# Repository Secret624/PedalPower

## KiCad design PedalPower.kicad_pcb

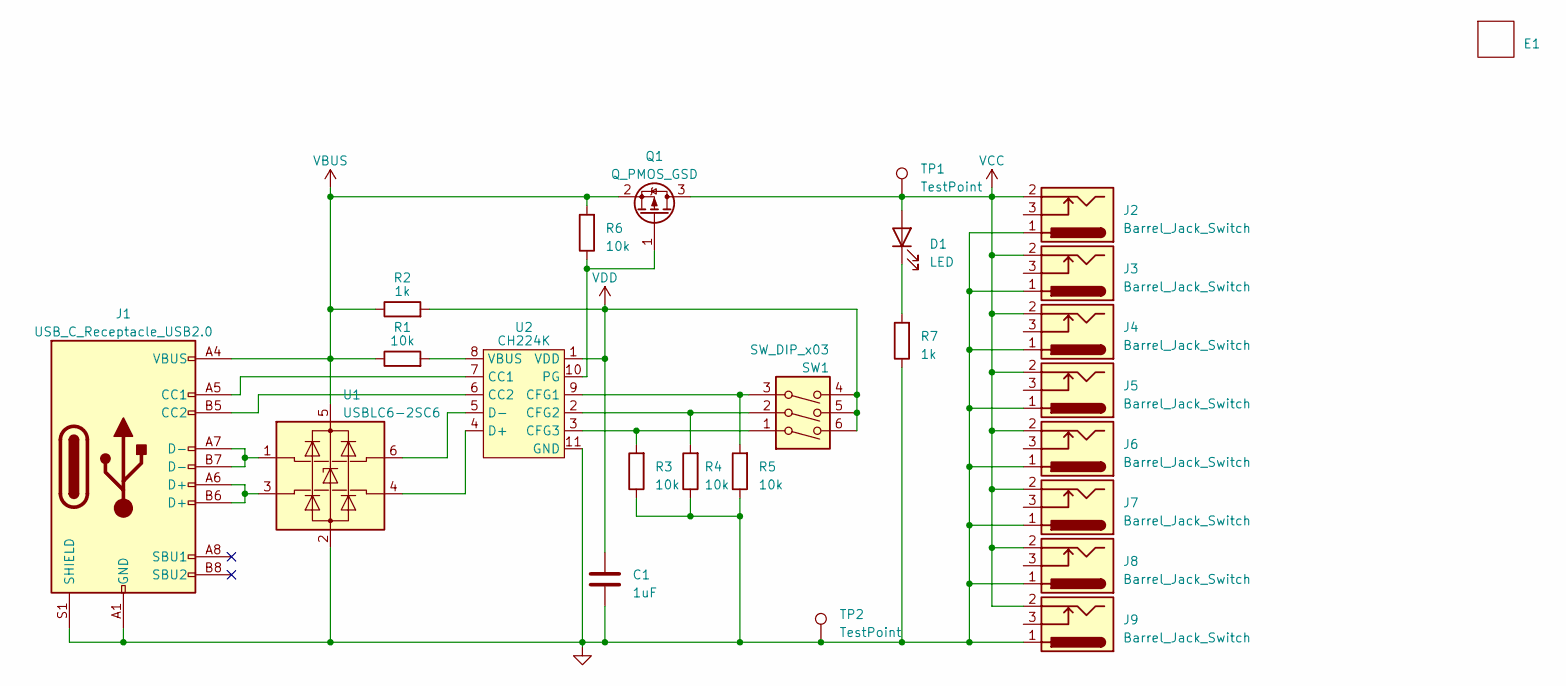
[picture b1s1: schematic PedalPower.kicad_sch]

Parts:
C1: 1uF; C_0805_2012Metric_Pad1.18x1.45mm_HandSolder
D1: LED; LED_0603_1608Metric_Pad1.05x0.95mm_HandSolder
E1: 1591XXMBK
J1: USB_C_Receptacle_USB2.0; USB_C_Receptacle_HRO_TYPE-C-31-M-12; LCSC# C165948
J2, J3, J4, J5, J6, J7, J8, J9: Barrel_Jack_Switch; BarrelJack_Wuerth_6941xx301002
Q1: Q_PMOS_GSD; SOT-23; LCSC# C840062
R1, R3, R4, R5, R6: 10k; R_0805_2012Metric_Pad1.20x1.40mm_HandSolder
R2: 1k; R_0805_2012Metric_Pad1.20x1.40mm_HandSolder
R7: 1k; R_1206_3216Metric_Pad1.30x1.75mm_HandSolder
SW1: SW_DIP_x03; SW_DIP_SPSTx03_Slide_6.7x9.18mm_W7.62mm_P2.54mm_LowProfile; LCSC# C3024969
TP1, TP2: TestPoint; TestPoint_THTPad_4.0x4.0mm_Drill2.0mm
U1: USBLC6-2SC6; SOT-23-6; LCSC# C2687116
U2: CH224K; SSOP-10_3.9x4.9mm_P1.00mm_EP_2.1x3.3; LCSC# C970725

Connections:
GND: C1.2, J1.A1 (GND), J1.A12 (GND), J1.B1 (GND), J1.B12 (GND), J1.S1 (SHIELD), J2.1, J3.1, J4.1, J5.1, J6.1, J7.1, J8.1, J9.1, R3.1, R4.1, R5.1, R7.1, TP2.1, U1.2 (GND), U2.11 (GND)
unnamed: D1.1 (K), R7.2
unnamed: J1.A5 (CC1), U2.7 (CC1)
unnamed: J1.B5 (CC2), U2.6 (CC2)
unnamed: J1.A6 (D+), J1.B6 (D+), U1.3 (I/O1)
unnamed: J1.A7 (D-), J1.B7 (D-), U1.1 (I/O1)
unnamed: Q1.1 (G), R6.1, U2.10 (PG)
unnamed: R5.2, SW1.3, U2.9 (CFG1)
unnamed: R4.2, SW1.2, U2.2 (CFG2)
unnamed: R3.2, SW1.1, U2.3 (CFG3)
unnamed: U1.4 (I/O2), U2.4 (D+)
unnamed: U1.6 (I/O2), U2.5 (D-)
unnamed: R1.2, U2.8 (VBUS)
VBUS: J1.A4 (VBUS), J1.A9 (VBUS), J1.B4 (VBUS), J1.B9 (VBUS), Q1.2 (S), R1.1, R2.1, R6.2, U1.5 (VBUS)
VCC: D1.2 (A), J2.2, J3.2, J4.2, J5.2, J6.2, J7.2, J8.2, J9.2, Q1.3 (D), TP1.1
VDD: C1.1, R2.2, SW1.4, SW1.5, SW1.6, U2.1 (VDD)

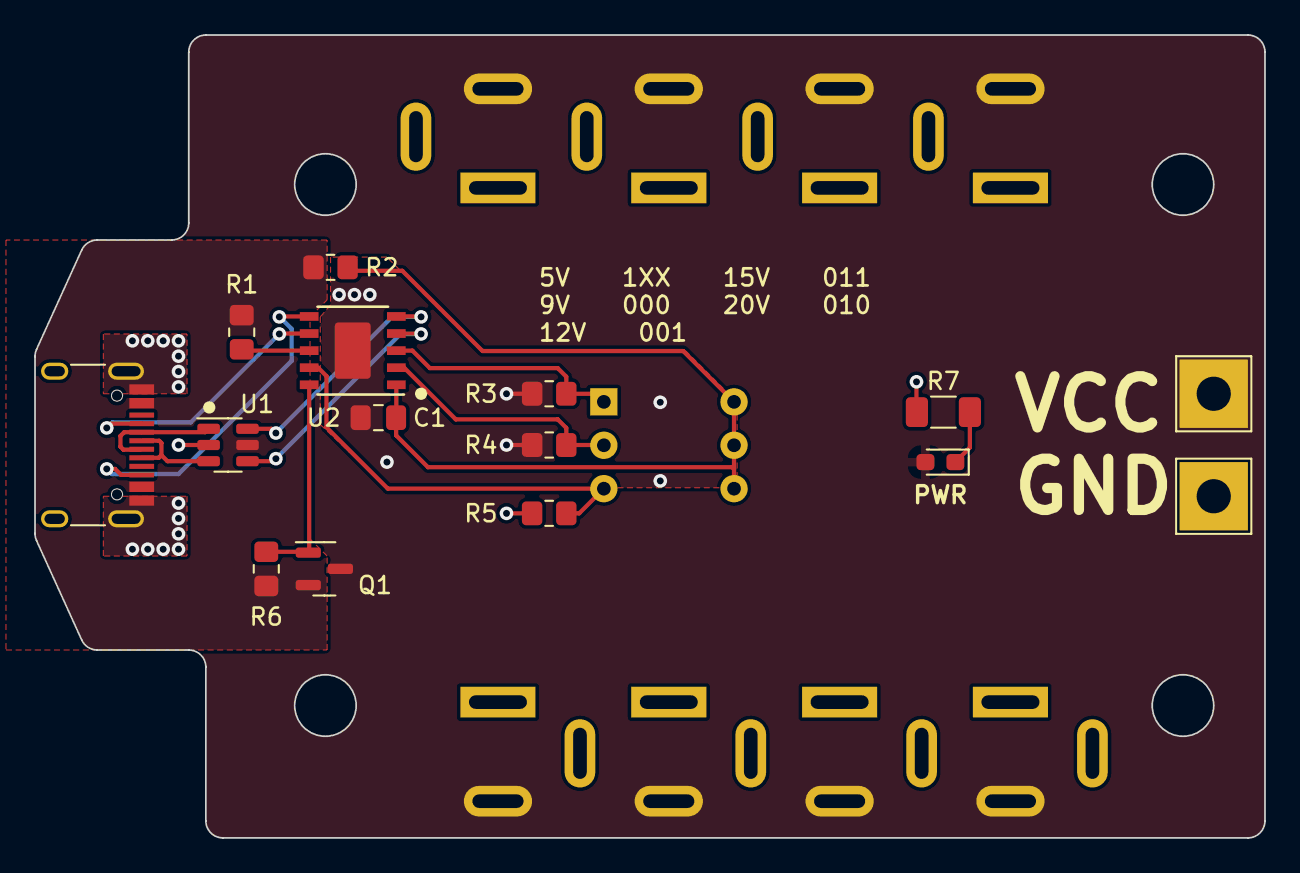
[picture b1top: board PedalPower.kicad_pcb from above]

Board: 2 copper layers, 72.0 x 47.0 mm, 25 parts (0 on the bottom side), 16 nets.
